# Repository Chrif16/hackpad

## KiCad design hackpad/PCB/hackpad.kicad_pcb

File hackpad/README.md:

# hackpad
hackpad for hackclub blueprint i made in 17 hours
# CAD:
here's what it looks like:

i made it in fusion 360 about a month ago
# pcb:

this is what i came up with i hope it works
# firmware:
i used QMK's firmware, this proved to be the most confusing hardest part of the project in my opinion thats why i left it on hold for a long time but i managed to figure it out eventually
# BOM:
4x DSA Keycaps
1x XIAO RP2040
1x Case (2 3d printed parts)
4x Cherry MX Switches(or any switch as long as it works)
4x screws (optional)

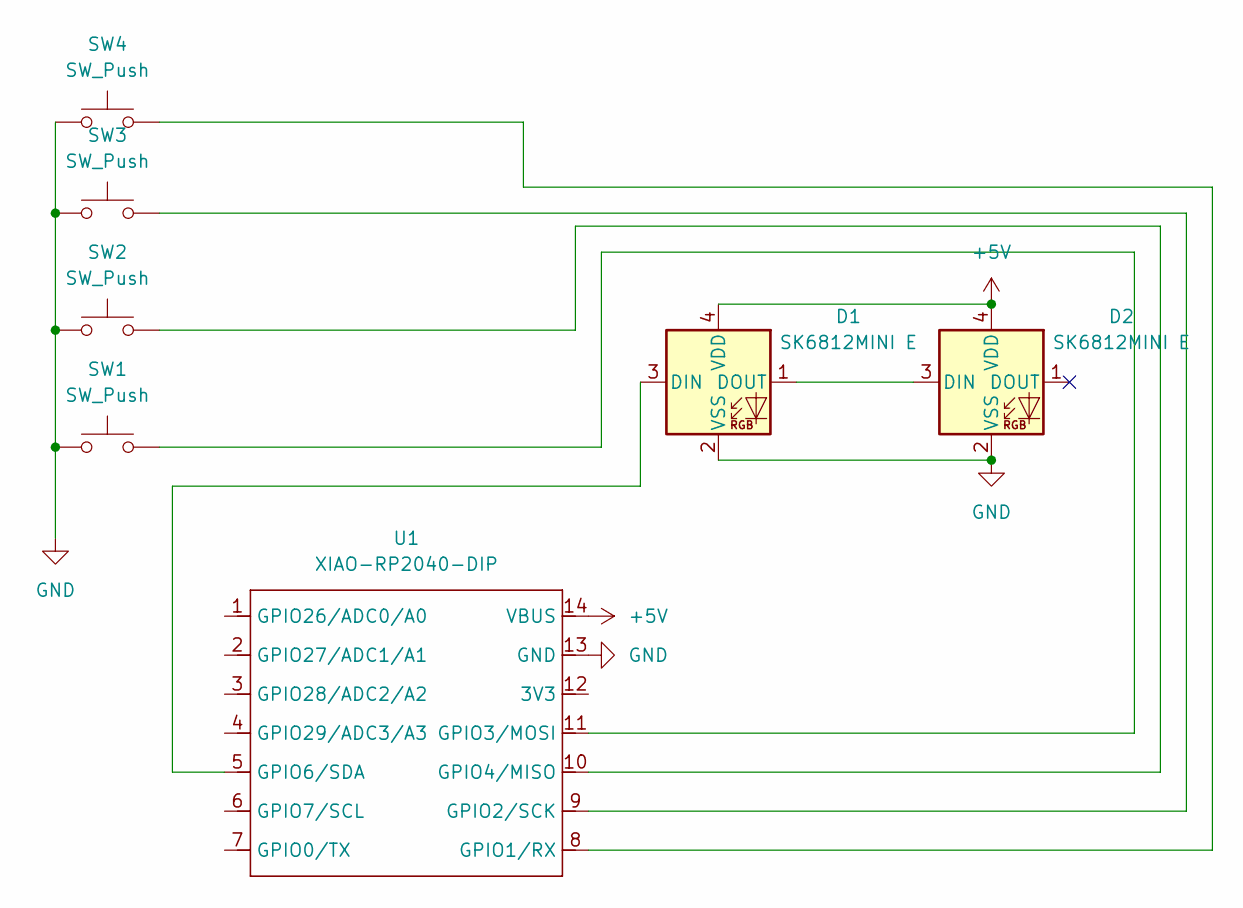
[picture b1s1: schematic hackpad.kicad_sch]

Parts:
D1, D2: SK6812MINI E; LED_SK6812-E
SW1, SW2, SW3, SW4: SW_Push; SW_Cherry_MX_1.00u_PCB
U1: XIAO-RP2040-DIP

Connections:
+5V: D1.4 (VDD), D2.4 (VDD), U1.14 (VBUS)
GND: D1.2 (VSS), D2.2 (VSS), SW1.1, SW2.1, SW3.1, SW4.1, U1.13 (GND)
unnamed: D1.3 (DIN), U1.5 (GPIO6/SDA)
unnamed: D1.1 (DOUT), D2.3 (DIN)
unnamed: SW4.2, U1.8 (GPIO1/RX)
unnamed: SW3.2, U1.9 (GPIO2/SCK)
unnamed: SW1.2, U1.11 (GPIO3/MOSI)
unnamed: SW2.2, U1.10 (GPIO4/MISO)

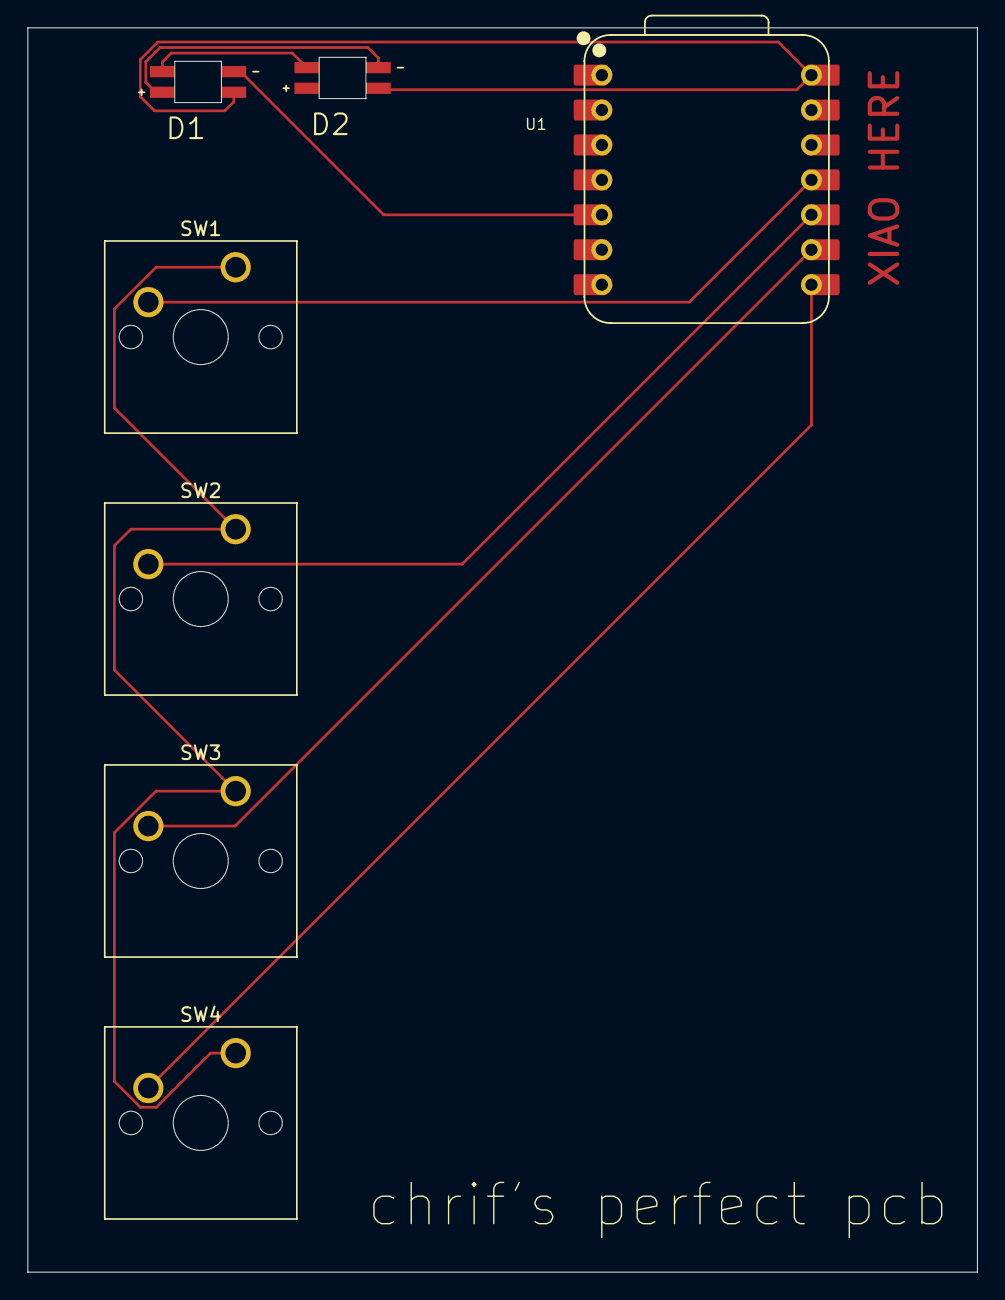
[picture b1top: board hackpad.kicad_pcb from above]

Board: 2 copper layers, 69.1 x 90.5 mm, 7 parts (0 on the bottom side), 8 nets.

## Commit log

2026-03-18 fix: add actual files
